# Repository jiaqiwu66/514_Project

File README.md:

Presentation file: https://docs.google.com/presentation/d/15DO_LJguWLzR6hT5lKLDi5ZQoy1D3yug2rMx-fKbxiI/edit?usp=sharing

Architecture System:

Solution Overview:

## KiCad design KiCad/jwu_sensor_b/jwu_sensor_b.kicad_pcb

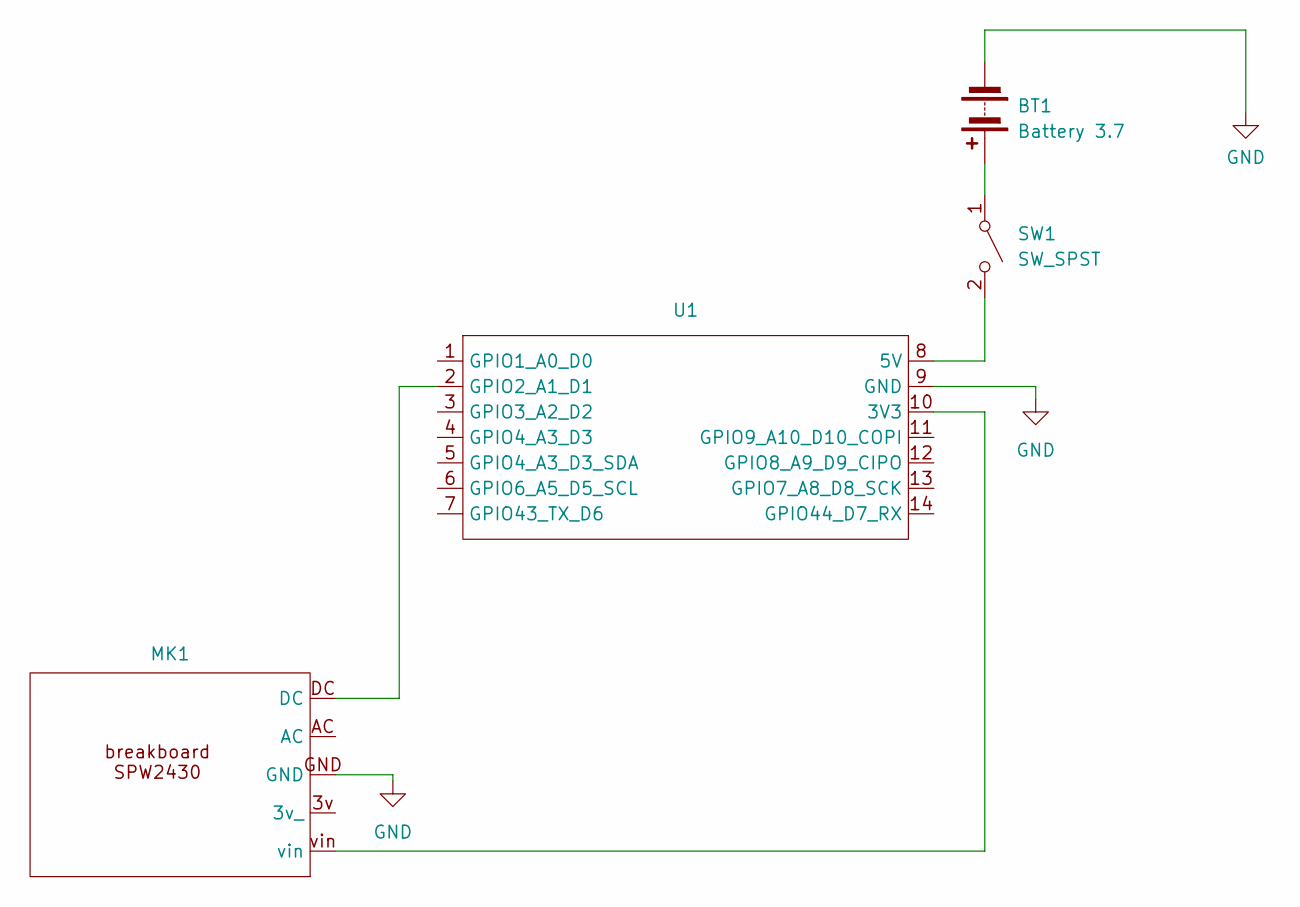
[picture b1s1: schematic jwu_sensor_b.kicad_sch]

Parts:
BT1: Battery 3.7; JST_PH_B2B-PH-K_1x02_P2.00mm_Vertical
MK1: spw-2430-brd
SW1: SW_SPST; SW_PUSH_6mm
U1: XIAO_ESP32_SENSE

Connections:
GND: BT1.2 (-), MK1.GND, U1.9 (GND)
unnamed: BT1.1 (+), SW1.1 (A)
unnamed: SW1.2 (B), U1.8 (5V)
unnamed: MK1.vin, U1.10 (3V3)
unnamed: MK1.DC, U1.2 (GPIO2_A1_D1)

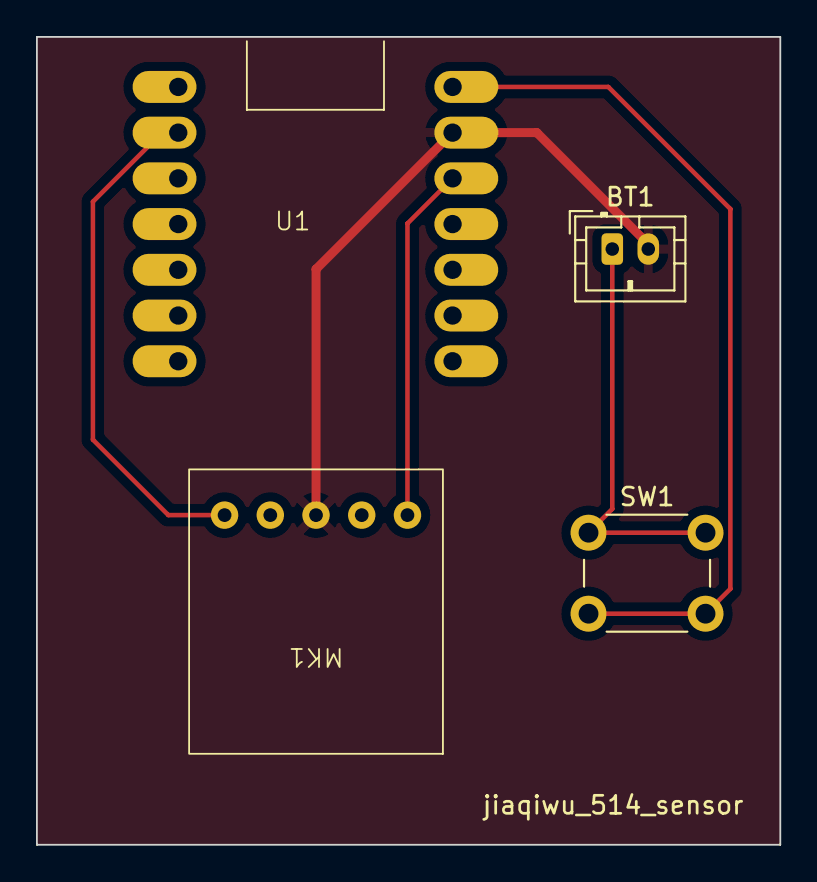
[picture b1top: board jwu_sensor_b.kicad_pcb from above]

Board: 2 copper layers, 41.3 x 44.9 mm, 4 parts (0 on the bottom side), 5 nets.

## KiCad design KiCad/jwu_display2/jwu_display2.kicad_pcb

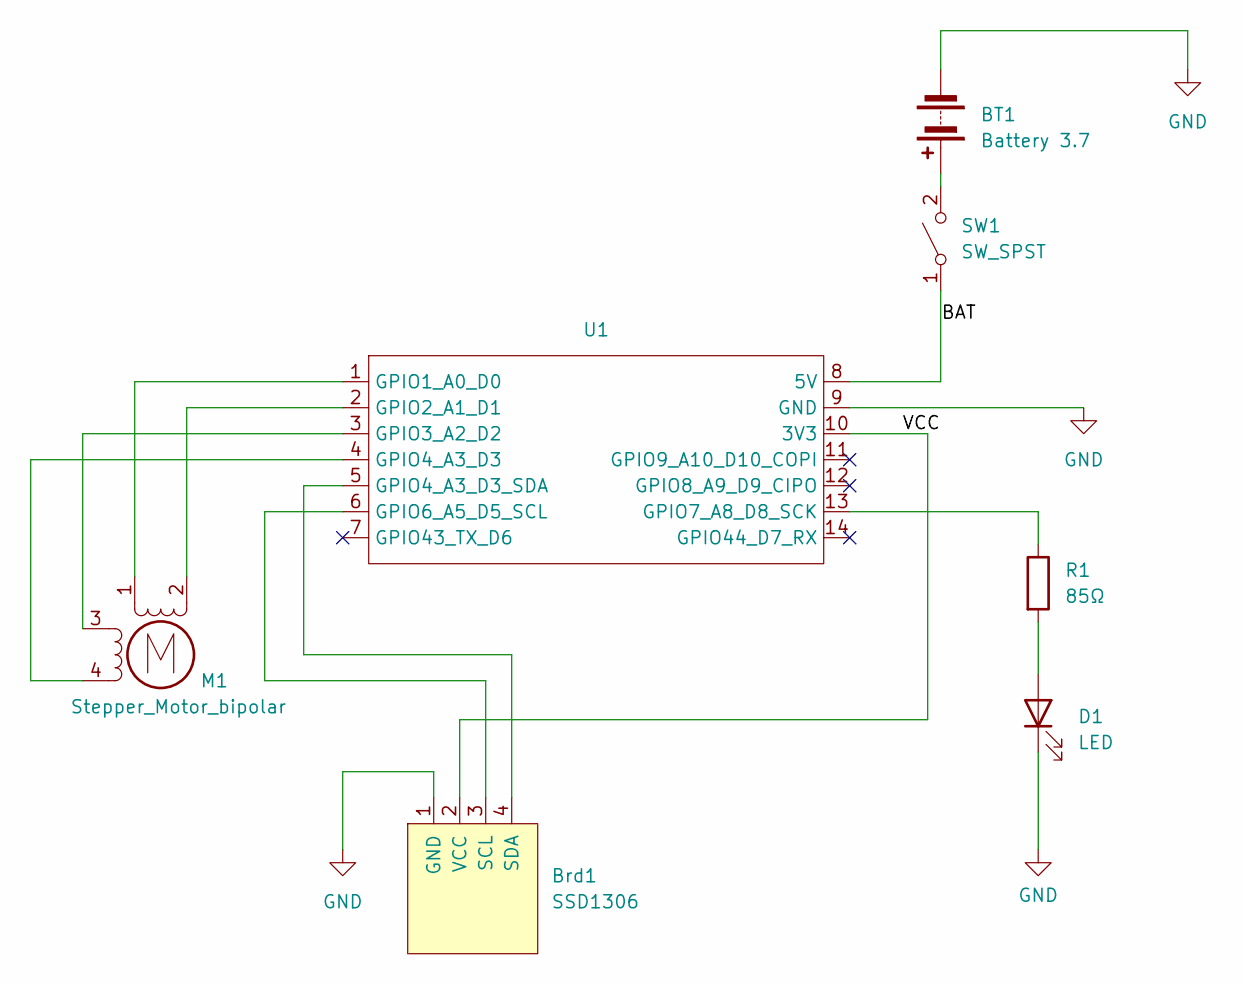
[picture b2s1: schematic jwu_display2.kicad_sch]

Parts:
BT1: Battery 3.7; JST_PH_B2B-PH-K_1x02_P2.00mm_Vertical
Brd1: SSD1306; 128x64OLED
D1: LED; LED_0805_2012Metric_Pad1.15x1.40mm_HandSolder
M1: Stepper_Motor_bipolar; x27_stepper_two_holes
R1: 85Ω; R_0603_1608Metric_Pad0.98x0.95mm_HandSolder
SW1: SW_SPST; SW_PUSH_6mm
U1: XIAO_ESP32_SENSE

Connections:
/BAT: SW1.1 (A), U1.8 (5V)
/VCC: Brd1.2 (VCC), U1.10 (3V3)
GND: BT1.2 (-), Brd1.1 (GND), D1.1 (K), U1.9 (GND)
unnamed: BT1.1 (+), SW1.2 (B)
unnamed: Brd1.3 (SCL), U1.6 (GPIO6_A5_D5_SCL)
unnamed: Brd1.4 (SDA), U1.5 (GPIO4_A3_D3_SDA)
unnamed: D1.2 (A), R1.2
unnamed: M1.2 (-), U1.2 (GPIO2_A1_D1)
unnamed: M1.1, U1.1 (GPIO1_A0_D0)
unnamed: M1.3, U1.3 (GPIO3_A2_D2)
unnamed: M1.4, U1.4 (GPIO4_A3_D3)
unnamed: R1.1, U1.13 (GPIO7_A8_D8_SCK)

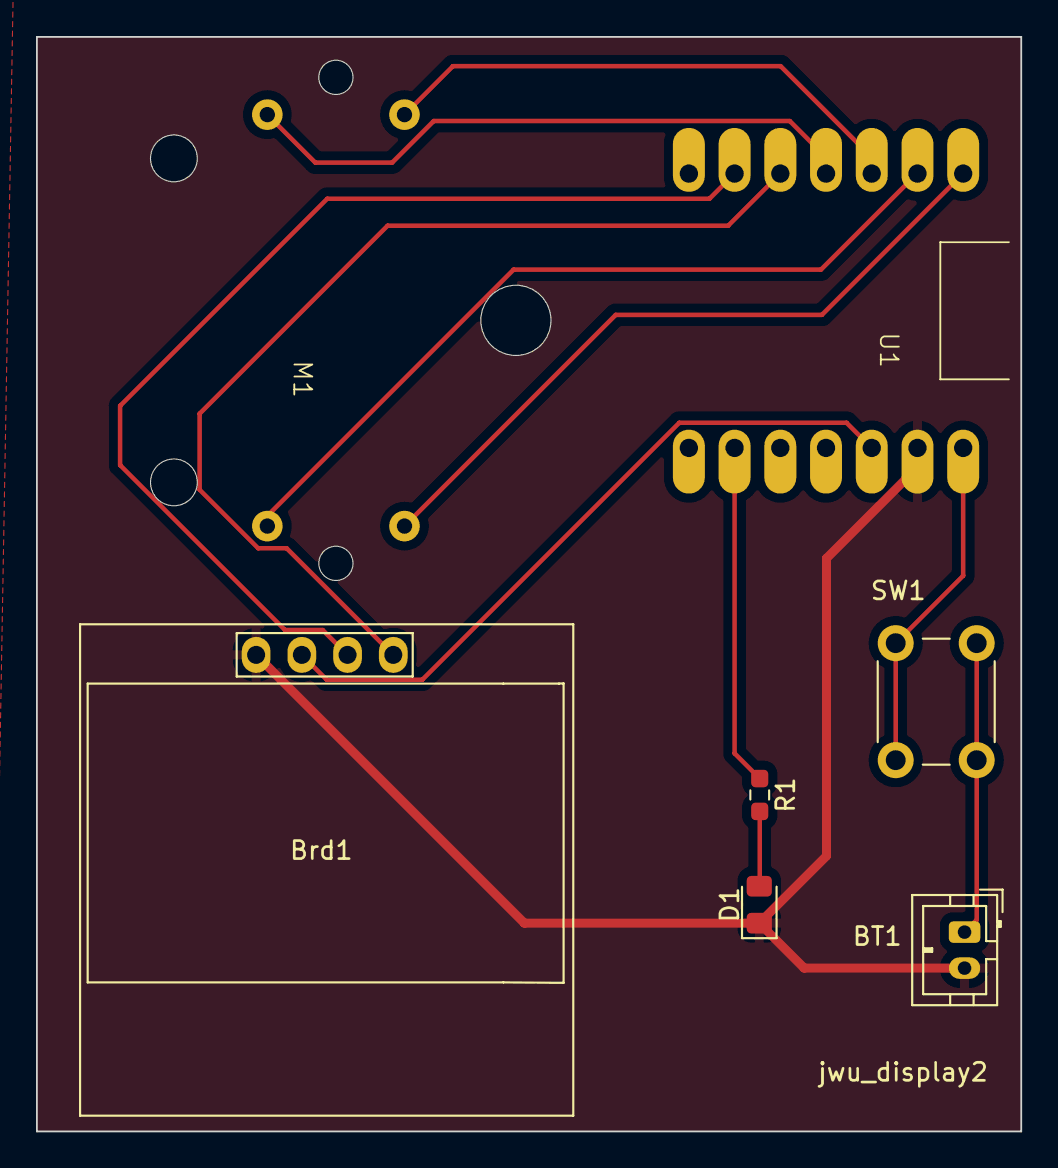
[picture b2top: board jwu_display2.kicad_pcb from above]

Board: 2 copper layers, 54.7 x 60.8 mm, 7 parts (0 on the bottom side), 12 nets.

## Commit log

2024-01-14 commit folder
2024-01-14 commit update
2024-01-14 add README and datasheet
2024-01-14 update display datasheet
2024-01-17 Update README.md
    add description for sensor devices
2024-01-17 Update README.md for display description
2024-01-17 Update README.md add diagram
2024-01-17 Update README.md modify work detail diagram
2024-01-17 Update README.md add sketch
2024-01-18 add datasheet
2024-01-18 add schematic file
2024-02-06 Add ESP-32
2024-02-06 Add battery estimate file
2024-02-06 datasheet for sensor
2024-02-07 add datasheet for sensor
2024-03-03 upload code for final
2024-03-06 final file update
2024-03-06 add README
